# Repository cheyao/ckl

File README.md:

# ckl

An assortiment useful footprints and symbols for digital designs.

Currently contains 65 footprints and 68 symbols.

## How to install

Open the KiCad "Plugin and Content Manager" (referred to as "PCM" from now on) and click on "Manage". Add a new entry with the plus sign and paste

```
https://raw.githubusercontent.com/cheyao/cyao-kicad-repo/main/repository.json
```

From this point on you will have "cyao KiCad repository" in your drop-down selection, and it will allow you to install (and update) ckl through PCM - easy and hassle-free.

## Disclaimer

### **We do not assume any responsibility for broken PCBs or damages derived from errors in this library. Use at your own risk, and please open an issue or pull-request if you encounter any errors.**

Please do not use any footprint from this library with a symbol from another library (or the other way round). Pin numbering conventions are not always the same, and unless you check very carefully this can lead to broken PCBs.

## Credits

The repo structure was largely inspired by ebastler's https://github.com/ebastler/ebastler-kicad-repository

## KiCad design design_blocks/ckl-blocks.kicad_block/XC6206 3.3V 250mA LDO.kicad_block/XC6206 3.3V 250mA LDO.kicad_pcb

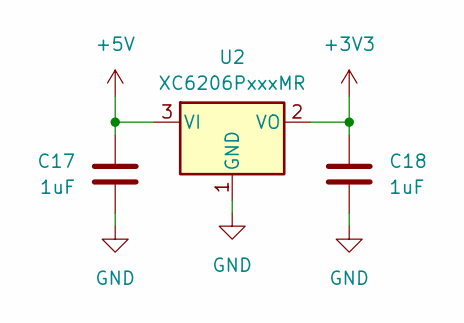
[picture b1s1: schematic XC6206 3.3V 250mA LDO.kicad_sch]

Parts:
C17, C18: 1uF; C_0402_1005Metric; LCSC Part # C52923
U2: XC6206PxxxMR; SOT-23-3; LCSC Part # C5446

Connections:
+3V3: C18.1, U2.2 (VO)
+5V: C17.1, U2.3 (VI)
GND: C17.2, C18.2, U2.1 (GND)

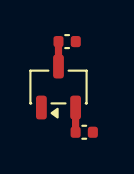
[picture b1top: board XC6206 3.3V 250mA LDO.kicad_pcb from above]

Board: 2 copper layers, 3 parts (0 on the bottom side), 3 nets.

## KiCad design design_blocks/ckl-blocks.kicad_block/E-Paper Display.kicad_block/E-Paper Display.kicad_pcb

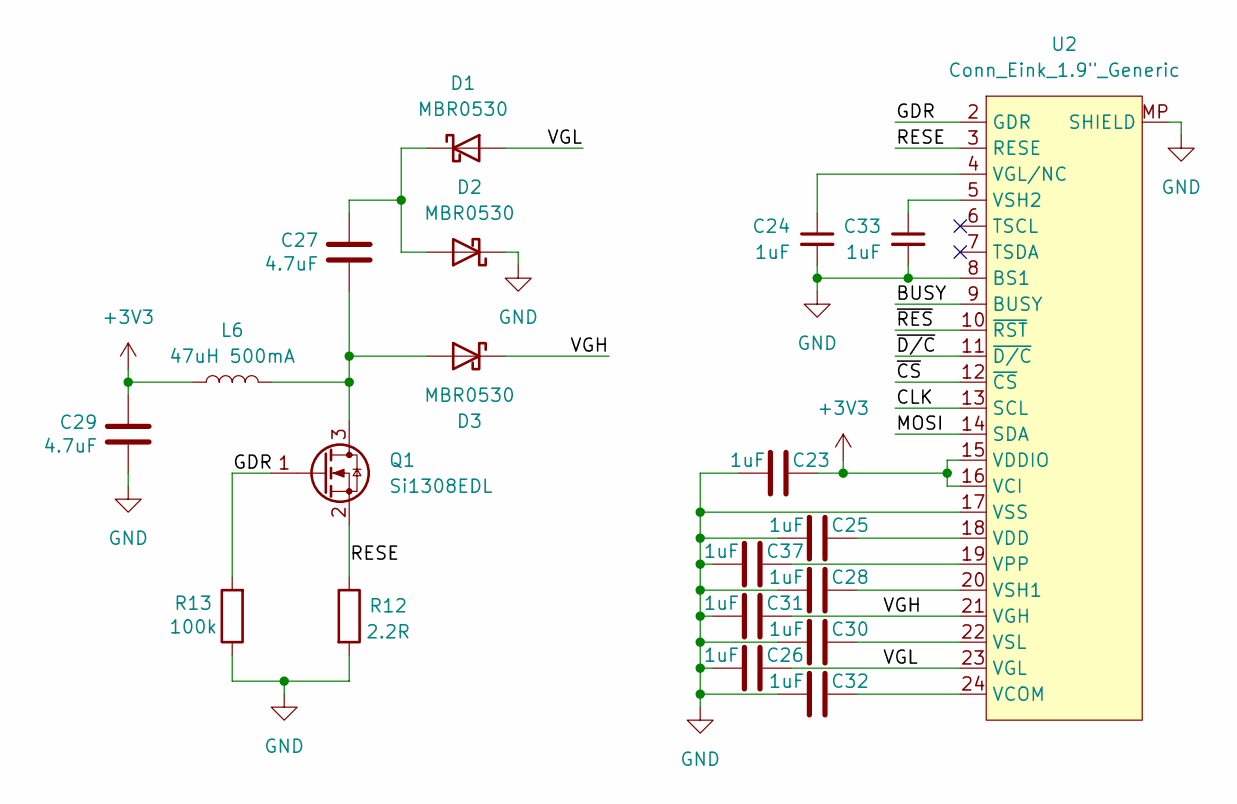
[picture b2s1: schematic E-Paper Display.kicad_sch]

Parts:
C23, C24, C25, C26, C28, C30, C31, C32, C33, C37: 1uF; C_0402_1005Metric; LCSC Part # C7472946
C27, C29: 4.7uF; C_0402_1005Metric; LCSC Part # C380302
D1, D2, D3: MBR0530; D_SOD-123; LCSC Part # C82046
L6: 47uH 500mA; L_APV_ANR3015; LCSC Part # C7427088
Q1: Si1308EDL; SOT-323_SC-70; LCSC Part # C7603347
R12: 2.2R; R_0402_1005Metric; LCSC Part # C2906922
R13: 100k; R_0402_1005Metric; LCSC Part # C481918
U2: Conn_Eink_1.9"_Generic; HCTL_HC-FPC-05-09-24RLTAG-1MP_P0.5mm_Horizontal; LCSC Part # C5213757

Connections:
+3V3: C23.1, C29.1, L6.1, U2.15 (VDDIO), U2.16 (VCI)
/BUSY: U2.9 (BUSY)
/CLK: U2.13 (SCL)
/GDR: Q1.1 (G), R13.2, U2.2 (GDR)
/MOSI: U2.14 (SDA)
/RESE: Q1.2 (S), R12.1, U2.3 (RESE)
/VGH: C31.1, D3.1 (K), U2.21 (VGH)
/VGL: C26.1, D1.2 (A), U2.23 (VGL)
/~CS: U2.12 (~CS)
/~D/C: U2.11 (~D/C)
/~RES: U2.10 (~RST)
GND: C23.2, C24.2, C25.2, C26.2, C28.2, C29.2, C30.2, C31.2, C32.2, C33.2, C37.2, D2.1 (K), R12.2, R13.1, U2.8 (BS1), U2.17 (VSS), U2.MP (SHIELD)
unnamed: C27.1, D1.1 (K), D2.2 (A)
unnamed: C27.2, D3.2 (A), L6.2, Q1.3 (D)
unnamed: C32.1, U2.24 (VCOM)
unnamed: C25.1, U2.18 (VDD)
unnamed: C24.1, U2.4 (VGL/NC)
unnamed: C37.1, U2.19 (VPP)
unnamed: C28.1, U2.20 (VSH1)
unnamed: C33.1, U2.5 (VSH2)
unnamed: C30.1, U2.22 (VSL)

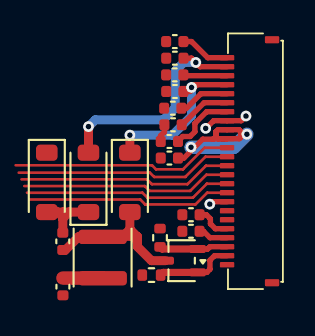
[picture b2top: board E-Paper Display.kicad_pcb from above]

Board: 4 copper layers, 20 parts (0 on the bottom side), 15 nets.

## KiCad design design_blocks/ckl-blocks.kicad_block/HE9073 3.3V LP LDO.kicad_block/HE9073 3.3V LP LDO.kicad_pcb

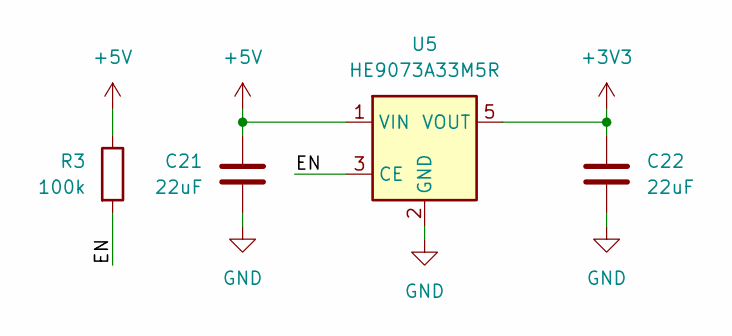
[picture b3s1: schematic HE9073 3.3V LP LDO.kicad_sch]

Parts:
C21, C22: 22uF; C_0603_1608Metric; LCSC Part # C380323
R3: 100k; R_0402_1005Metric; LCSC Part # C481918
U5: HE9073A33M5R; SOT-23-5; LCSC Part # C723789

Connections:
+3V3: C22.1, U5.5 (VOUT)
+5V: C21.1, R3.1, U5.1 (VIN)
/EN: R3.2, U5.3 (CE)
GND: C21.2, C22.2, U5.2 (GND)

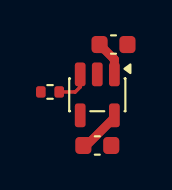
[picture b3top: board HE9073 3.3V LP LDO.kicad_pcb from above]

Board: 4 copper layers, 4 parts (0 on the bottom side), 4 nets.

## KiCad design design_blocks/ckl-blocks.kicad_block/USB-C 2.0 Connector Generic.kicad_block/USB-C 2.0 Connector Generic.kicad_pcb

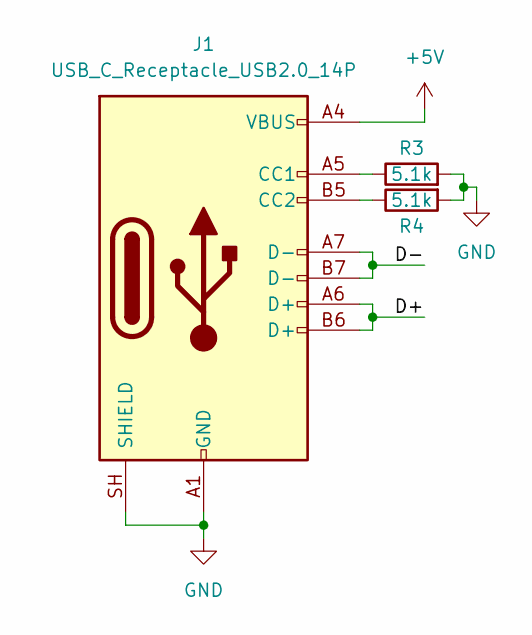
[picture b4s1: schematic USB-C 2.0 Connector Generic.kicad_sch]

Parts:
J1: USB_C_Receptacle_USB2.0_14P; USB_C_Receptacle_HRO_TYPE-C-31-M-12; LCSC Part # C393939
R3, R4: 5.1k; R_0402_1005Metric; LCSC Part # C25905

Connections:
+5V: J1.A4 (VBUS), J1.A9 (VBUS), J1.B4 (VBUS), J1.B9 (VBUS)
/D+: J1.A6 (D+), J1.B6 (D+)
/D-: J1.A7 (D-), J1.B7 (D-)
GND: J1.A1 (GND), J1.A12 (GND), J1.B1 (GND), J1.B12 (GND), J1.SH (SHIELD), R3.2, R4.2
unnamed: J1.A5 (CC1), R3.1
unnamed: J1.B5 (CC2), R4.1

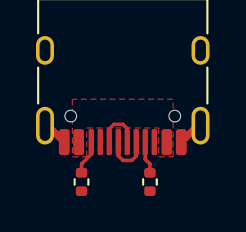
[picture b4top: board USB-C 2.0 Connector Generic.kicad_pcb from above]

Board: 2 copper layers, 3 parts (0 on the bottom side), 6 nets.

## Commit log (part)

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2026-06-10 First batch of symbols & footprints
2026-06-11 Second batch of symbols & footprints
2026-06-11 Final footprints
2026-06-11 Improve readme
2026-06-12 Fix 3d model paths
2026-06-13 Improve script
2026-06-21 Another bunch of footprints and symbols
2026-06-22 Castellated holes footpritns
2026-06-24 Change icon size
2026-06-27 Add design blocks
